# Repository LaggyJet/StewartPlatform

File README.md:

# Stewart Platform

This repository contains all files related to the **Stewart Platform** project.

## 📁 Contents

- CAD files  
- Arduino `.ino` script  
- EAGLE files  

> ⚠️ **Note:** Some **SolidWorks** relations may be broken. Please double-check mate constraints and resolve any rebuild errors when opening the assembly.

## 🛠️ About the Stewart Platform

A Stewart Platform (also known as a hexapod) is a type of parallel robot commonly used for motion simulation, precise positioning, and vibration isolation. It uses six actuators to control the platform’s position and orientation in 3D space.

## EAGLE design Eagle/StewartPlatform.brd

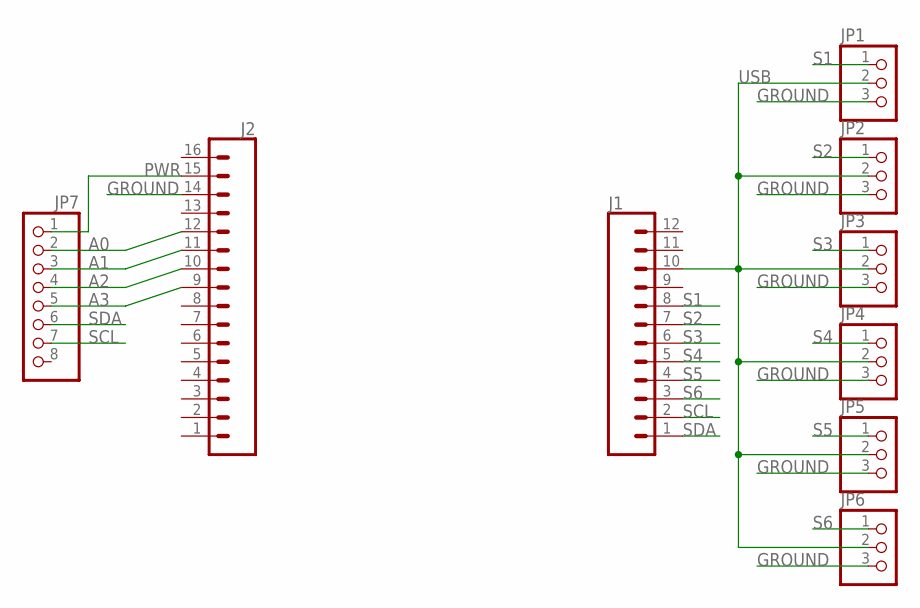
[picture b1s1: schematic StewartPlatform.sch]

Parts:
J1: SPARKFUN-CONNECTORS_CONN_12; SPARKFUN-CONNECTORS_1X12
J2: SPARKFUN-CONNECTORS_CONN_16; SPARKFUN-CONNECTORS_1X16
JP1, JP2, JP3, JP4, JP5, JP6: RARNDT-MISCELANEOUS_PINHD-1X3; RARNDT-MISCELANEOUS_1X03
JP7: PINHD-1X8; 1X08

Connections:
A0: J2.12, JP7.2
A1: J2.11, JP7.3
A2: J2.10, JP7.4
A3: J2.9, JP7.5
GROUND: J2.14, JP1.3, JP2.3, JP3.3, JP4.3, JP5.3, JP6.3
PWR: J2.15, JP7.1
S1: J1.8, JP1.1
S2: J1.7, JP2.1
S3: J1.6, JP3.1
S4: J1.5, JP4.1
S5: J1.4, JP5.1
S6: J1.3, JP6.1
SCL: J1.2, JP7.7
SDA: J1.1, JP7.6
USB: J1.10, JP1.2, JP2.2, JP3.2, JP4.2, JP5.2, JP6.2

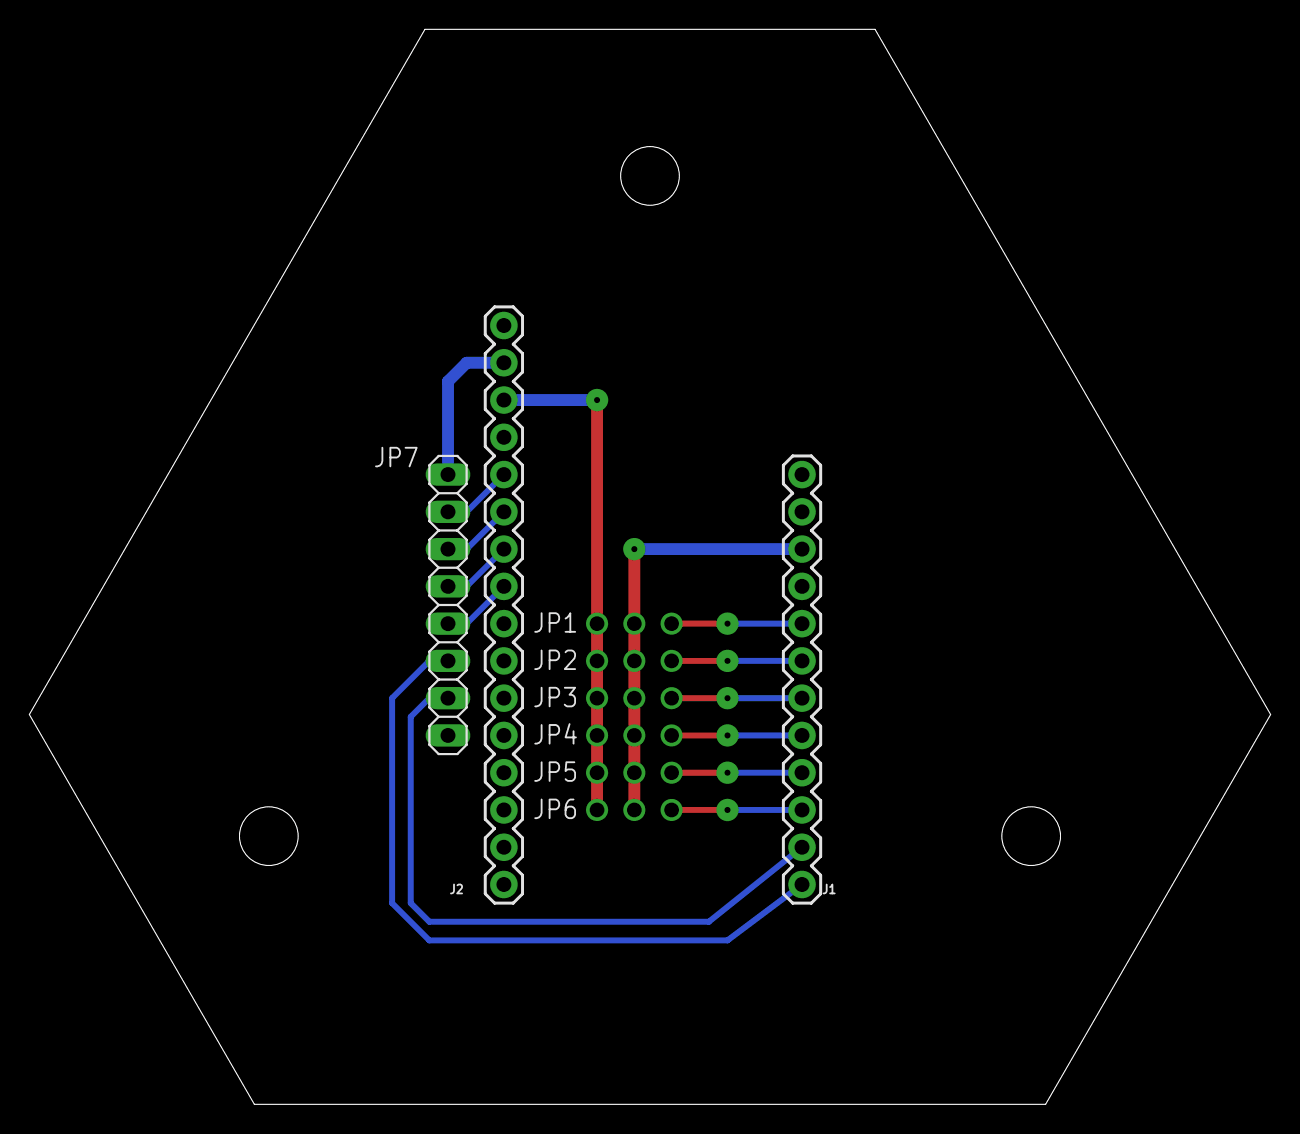
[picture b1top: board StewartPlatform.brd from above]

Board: 2 copper layers, 84.6 x 73.3 mm, 9 parts (0 on the bottom side), 15 nets.

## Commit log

2025-05-26 Init data push
